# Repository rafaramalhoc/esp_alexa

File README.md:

# esp_alexa
Interface de comunicação com Alexa para controle de iluminação.
Exemplo do funcionamento: https://www.youtube.com/watch?v=kryLgJ9ZHlE

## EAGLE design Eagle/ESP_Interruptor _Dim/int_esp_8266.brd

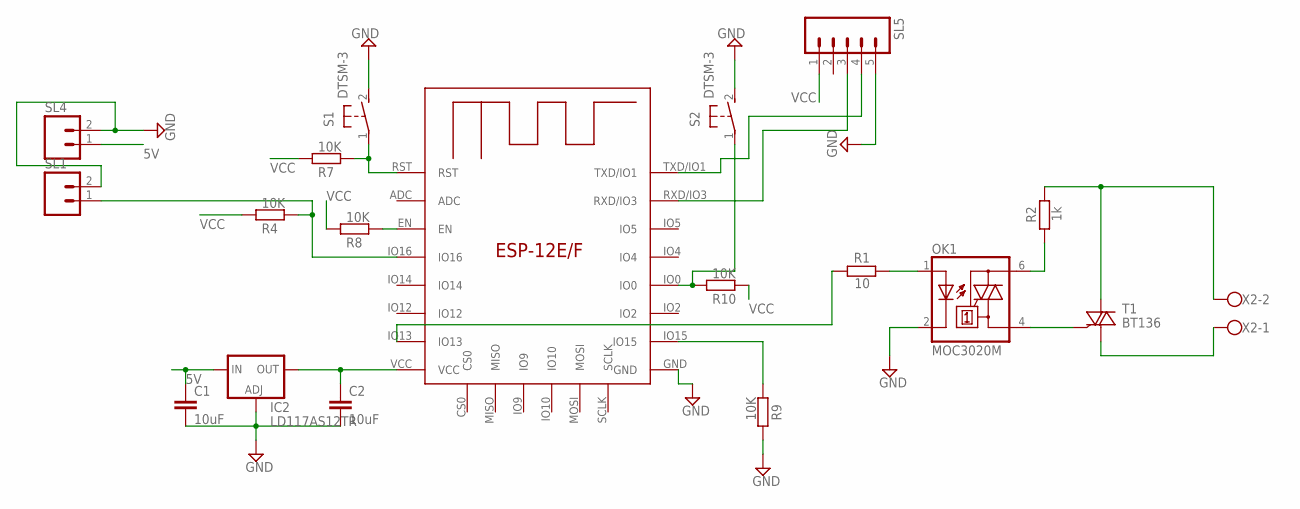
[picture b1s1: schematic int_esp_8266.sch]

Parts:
C1, C2: 10uF; C0805
IC1: ESP-12E/F; ESP-12E
IC2: LD117AS12TR; SOT223
OK1: MOC3020M; DIL06
R1: 10; M0805
R2: 1k; M0805
R4, R7, R8, R9, R10: 10K; M0805
S1, S2: DTSM-3
SL1, SL4: M02; 02P
SL5: M05; 05P
T1: BT136; TO220AB
X2: W237-102

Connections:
5V: C1.1, IC2.3 (IN), SL4.1
GND: C1.2, C2.2, IC1.GND, IC2.1 (ADJ), OK1.2 (C), R9.1, S1.2, S2.2, SL1.2, SL4.2, SL5.5
unnamed: IC1.IO13, R1.2
unnamed: OK1.4 (A1), T1.3 (G)
unnamed: IC1.IO15, R9.2
unnamed: OK1.1 (A), R1.1
unnamed: IC1.RST, R7.2, S1.1
unnamed: OK1.6 (A2), R2.2
unnamed: R2.1, T1.2 (A2), X2.2
unnamed: T1.1 (A1), X2.1
unnamed: IC1.IO16, R4.2, SL1.1
unnamed: IC1.EN, R8.2
unnamed: IC1.IO0, R10.1, S2.1
unnamed: IC1.RXD/IO3, SL5.3
unnamed: IC1.TXD/IO1, SL5.4
VCC: C2.1, IC1.VCC, IC2.4 (OUT), R4.1, R7.1, R8.1, R10.2, SL5.1

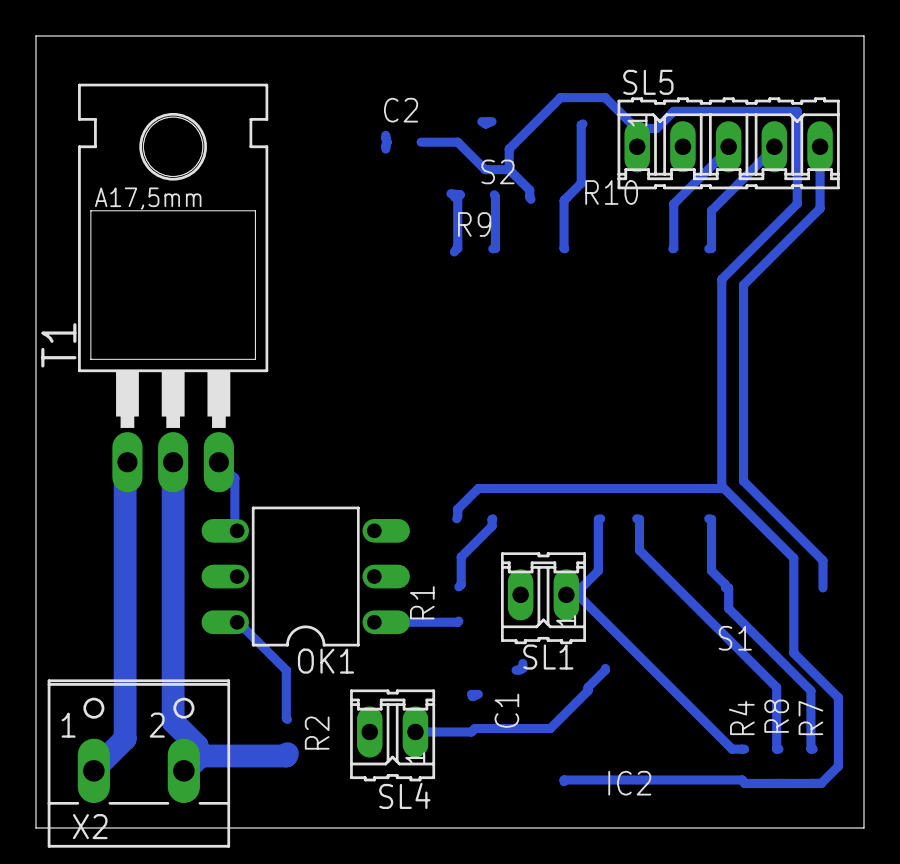
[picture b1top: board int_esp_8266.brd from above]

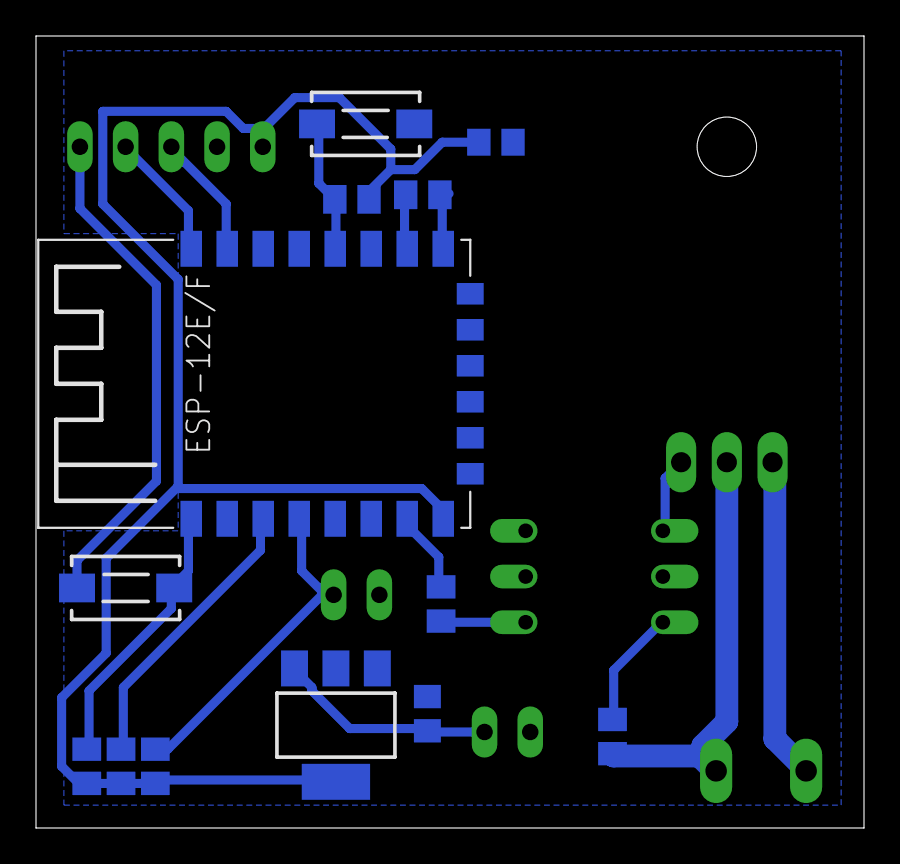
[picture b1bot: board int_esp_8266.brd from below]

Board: 2 copper layers, 46.0 x 44.0 mm, 19 parts (13 on the bottom side), 16 nets.

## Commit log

2022-06-12 Add files via upload
    Versão inicial do projeto
